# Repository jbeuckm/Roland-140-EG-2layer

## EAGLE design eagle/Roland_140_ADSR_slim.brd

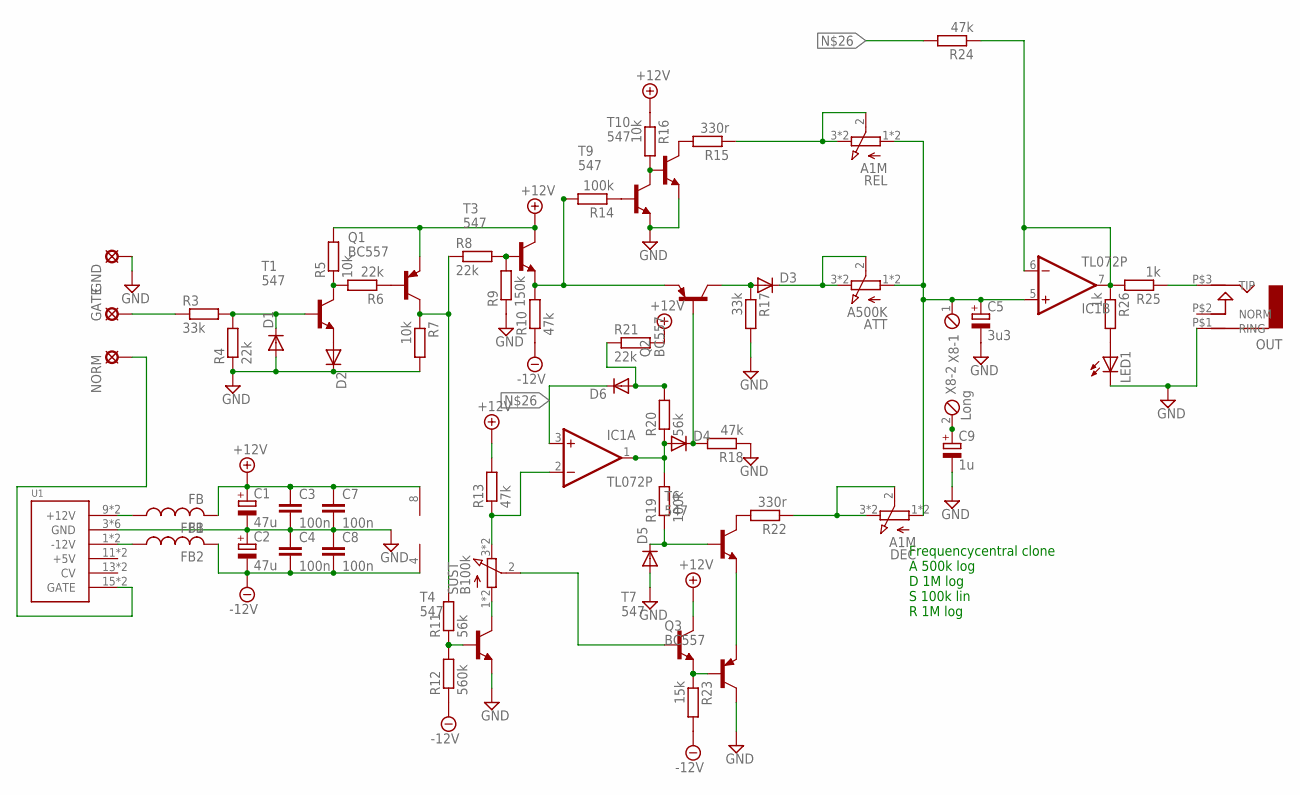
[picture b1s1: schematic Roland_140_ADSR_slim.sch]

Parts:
ATT: A500K; 3RP/1610N
C1, C2: 47u; E2,5-7
C3, C4: 100n; C025-025X050
C5: 3u3; E2,5-6
C7, C8: 100n; C1206K
C9: 1u; E2,5-6
D1, D2, D3, D4, D5, D6: 1N4148DO35-7; DO35-7
DEC: A1M; 3RP/1610N
FB1, FB2: FB
GATE: LSP10
GND: LSP10
IC1: TL072P; DIL08
LED1: LED3MM
NORM: LSP10
OUT: AUDIO-JACKITEAD; JACK-90DEG-ITEAD
Q1, Q2, Q3: BC557; TO92-EBC
R3, R17: 33k; 0204/7
R4, R6, R8, R21: 22k; 0204/7
R5, R7: 10k; 0204/7
R9: 150k; 0204/7
R10, R13, R18, R24: 47k; 0204/7
R11, R20: 56k; 0204/7
R12: 560k; 0204/7
R14, R19: 100k; 0204/7
R15: 330r; 0207/7
R16: 10k; 0207/7
R22: 330r; 0204/7
R23: 15k; 0204/7
R25, R26: 1k; 0204/7
REL: A1M; 3RP/1610N
SUST: B100k; 3RP/1610N
T1, T3, T4, T6, T7, T9, T10: 547; TO92-CBE
U1: POWER; POWER_16
X8: Long; 2POL254

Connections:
+12V: C1.+, C3.1, C7.1, FB1.P$2 (2), IC1.8 (V+), Q1.E, R5.2, R13.2, R16.1, R21.2, T3.C, T7.C
-12V: C2.-, C4.2, C8.2, FB2.P$2 (2), IC1.4 (V-), R10.1, R12.1, R23.2
GND: C1.-, C2.+, C3.2, C4.1, C5.-, C7.2, C8.1, C9.-, D1.A, D2.C, D5.A, GND.MP, LED1.K (C), OUT.P$1 (RING), Q3.C, R4.1, R7.2, R9.1, R17.2, R18.1, T4.E, T9.E, T10.E, U1.3 (GND), U1.4 (GND), U1.5 (GND), U1.6 (GND), U1.7 (GND), U1.8 (GND)
unnamed: OUT.P$3 (TIP), R25.1
unnamed: R14.1, T9.B
unnamed: R16.2, T9.C, T10.B
unnamed: R15.2, T10.C
unnamed: R15.1, REL.2 (S), REL.3 (E), REL.6 (E)
unnamed: SUST.1 (A), SUST.4 (A), T4.C
unnamed: D3.A, Q2.C, R17.1
unnamed: D4.C, Q2.B, R18.2
unnamed: D1.C, R3.2, R4.2, T1.B
unnamed: Q1.B, R6.1
unnamed: R5.1, R6.2, T1.C
unnamed: R11.1, R12.2, T4.B
unnamed: NORM.MP, U1.15 (GATE), U1.16 (GATE)
unnamed: IC1.2 (-IN), R13.1, SUST.3 (E), SUST.6 (E)
unnamed: D6.A, R20.2, R21.1
unnamed: D2.A, T1.E
unnamed: Q1.C, R7.1, R8.1, R11.2
unnamed: D4.A, IC1.1 (OUT), R19.2, R20.1
unnamed: R8.2, R9.2, T3.B
unnamed: Q2.E, R10.2, R14.2, T3.E
unnamed: D5.C, R19.1, T6.B
unnamed: R22.2, T6.C
unnamed: Q3.E, T6.E
unnamed: Q3.B, R23.1, T7.E
unnamed: SUST.2 (S), T7.B
unnamed: D6.C, IC1.3 (+IN), R24.2
unnamed: LED1.A, R26.2
unnamed: ATT.2 (S), ATT.3 (E), ATT.6 (E), D3.C
unnamed: DEC.2 (S), DEC.3 (E), DEC.6 (E), R22.1
unnamed: ATT.1 (A), ATT.4 (A), C5.+, DEC.1 (A), DEC.4 (A), IC1.5 (+IN), REL.1 (A), REL.4 (A), X8.1
unnamed: IC1.6 (-IN), IC1.7 (OUT), R24.1, R25.2, R26.1
unnamed: GATE.MP, R3.1
unnamed: C9.+, X8.2
unnamed: FB1.P$1 (1), U1.9 (+12V), U1.10 (+12V)
unnamed: FB2.P$1 (1), U1.1 (-12V), U1.2 (-12V)

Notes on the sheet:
Frequencycentral clone A 500k log D 1M log S 100k lin R 1M log

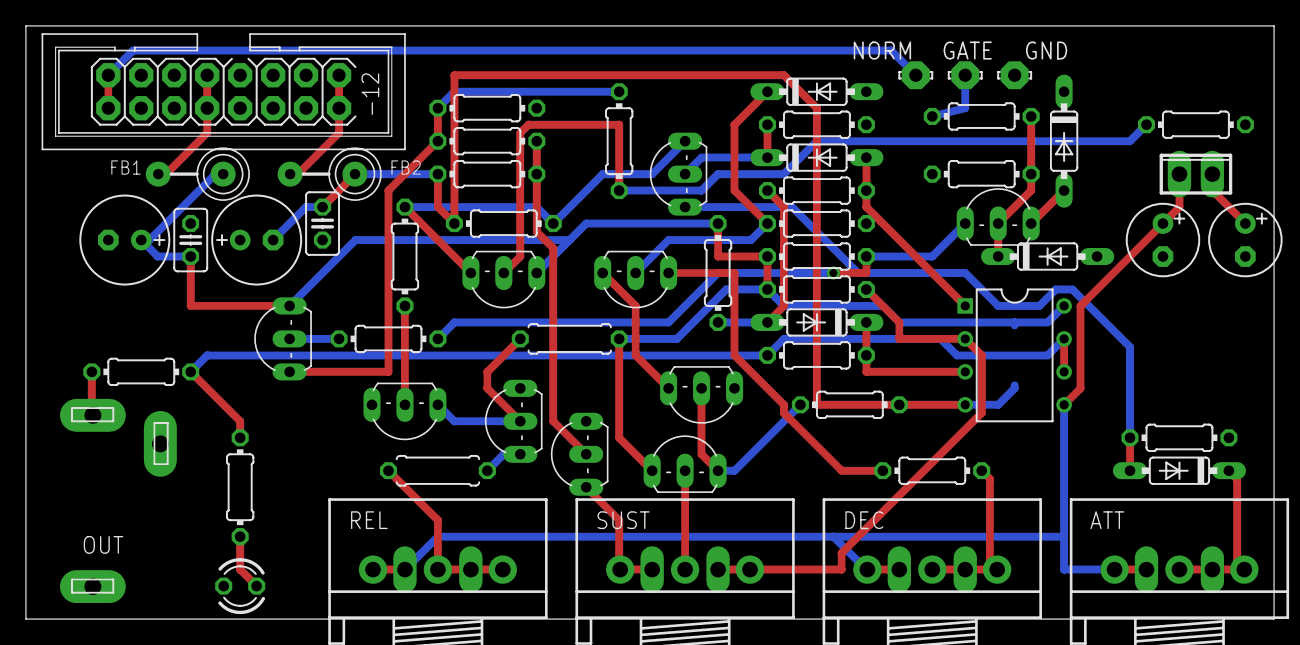
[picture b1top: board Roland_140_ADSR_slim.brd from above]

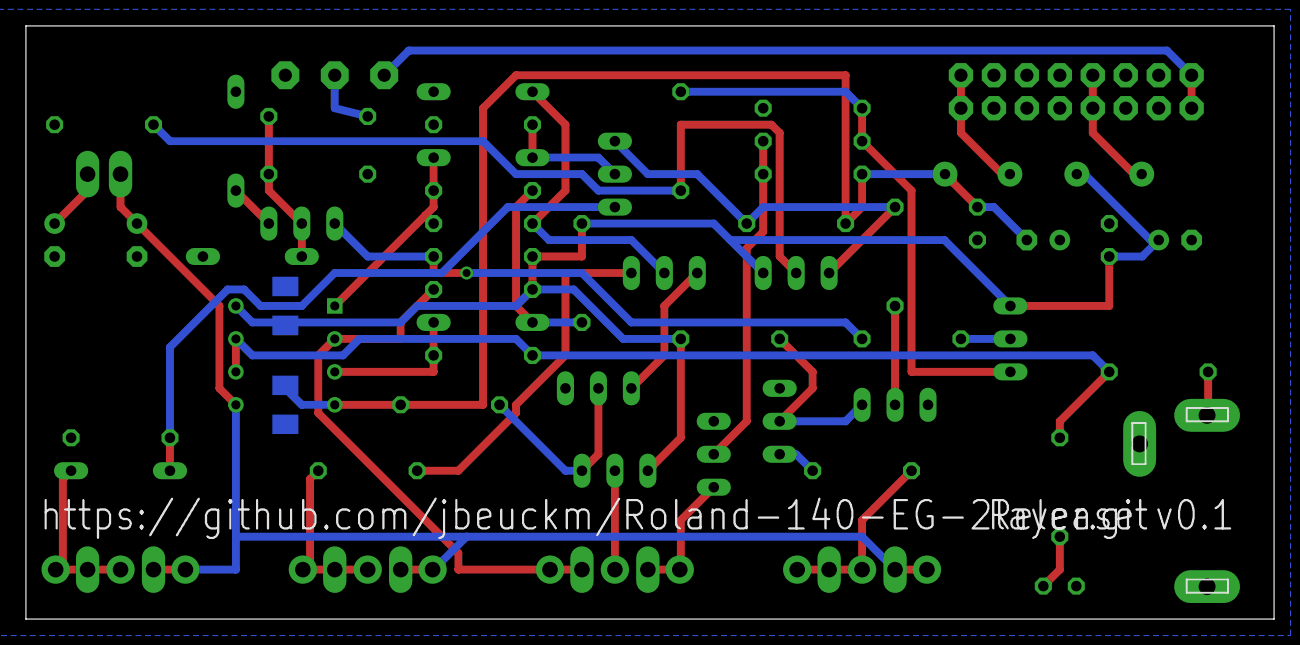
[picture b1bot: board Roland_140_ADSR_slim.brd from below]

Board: 2 copper layers, 96.1 x 45.6 mm, 62 parts (2 on the bottom side), 38 nets.

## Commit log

2017-09-03 routed and tweaked
2017-09-14 added labels for silkscreen
2017-09-16 added ground for gate input
2017-09-16 slightly shorter for room for gate input
2017-10-29 building a 3d printable panel in OpenSCAD
2017-10-29 cleaned up code
2017-10-30 knob labels
2017-12-18 updated panel to 3mm
